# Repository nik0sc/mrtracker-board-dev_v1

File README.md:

# mrtracker-board (dev_v1)

## What is this?

This is the KiCAD schematic and board layout of MRTracker. BOM and centroid (pick and place) files are in the `assembly` directory.

MRTracker is a physical map of the MRT that tracks the location of trains in near real-time. It is a PCB with an array of LEDs on them and an ESP32 that gets the real-time location of trains. An LED will be lit for every train currently on the network. Currently the North-South and East-West lines are supported.

In the background, there is a web service that polls SMRT’s train API and transforms the arrival times of all lines at all stations into a map of individual trains on the network. (So, the accuracy of train locations is determined by the accuracy of these arrival timings.) The MRTracker board retrieves the map from this service periodically.

If you’ve seen traintrackr.io then this is something like that, but adapted for Singapore.

[Here is Geoff Marshall explaining traintrackr](https://www.youtube.com/watch?v=676xnII2OZg)

## Can I make it?

Sure, but firmware is not included. I made the board you see at the start of this README with [JLCPCB](https://jlcpcb.com/), they're pretty great.

**As-is**: No warranty express or implied of fitness for purpose. 

## Can I fork it, remix it, add the other lines, etc...?

Generally there is no copyright enforceable for hardware designs (weirdly there is an exemption for the highly secretive and competitive world of photolithography mask designs). So feel free.

## Known issues

- USB port GND pin is not connected (grounds through shield)

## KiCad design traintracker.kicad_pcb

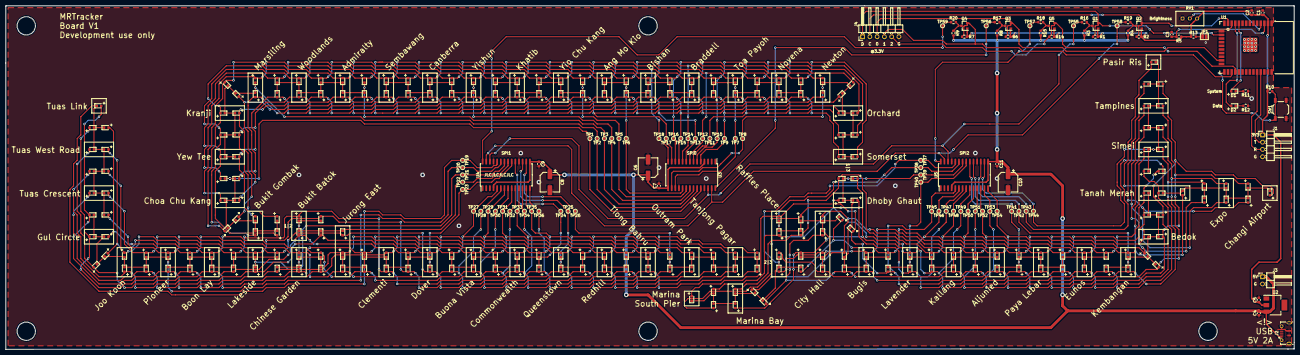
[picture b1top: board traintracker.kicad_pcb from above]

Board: 2 copper layers, 450.0 x 120.0 mm, 349 parts (0 on the bottom side), 82 nets.

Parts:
C1, C4, C5: 10uF; C_0603_1608Metric
C2, C7, C9, C11: 0.1uF; C_0603_1608Metric
C3: 1uF; C_0603_1608Metric
C6, C8, C10: 100uF; CP_Elec_6.3x5.3
D1, D3, D4, D5, D6, D7, D8, D9, D10, D11, D12, D13, D14, D15, D16, D17, D18, D19, D20, D21, D22, D23, D24, D25, D26, D27, D28, D29, D30, D31, D32, D33, D34, D35, D36, D37, D38, D39, D40, D41, D42, D43, D44, D45, D46, D47, D48, D49, D50, D51, D52, D53, D54, D55, D56, D57, D58, D59, D60, D61, D62, D63, D64, D65, D66, D67, D68, D69, D70, D71, D72, D73, D74, D75, D76, D77, D78, D79, D80, D81, D82, D118, D119, D120, D121, D122, D163, D164, D165, D166, D167, D168, D169, D173, D174, D175, D176, D178, D179, D182, D183, D184, D185, D186, D187: RED; LED_0603_1608Metric
D2, D83, D84, D85, D86, D87, D88, D89, D90, D91, D92, D93, D94, D95, D96, D97, D98, D99, D100, D101, D102, D103, D104, D105, D106, D107, D108, D109, D110, D111, D112, D113, D114, D115, D116, D117, D123, D124, D125, D126, D127, D128, D129, D130, D131, D132, D133, D134, D135, D136, D137, D138, D139, D140, D141, D142, D143, D144, D145, D146, D147, D148, D149, D150, D151, D152, D153, D154, D155, D156, D157, D158, D159, D160, D161, D162, D170, D171, D172, D177, D180, D181, D188, D189, D190, D191, D192, D193, D194, D195, D196, D197, D198, D199, D200, D201, D202, D203, D204, D205, D206, D207, D208, D209, D210, D211, D212, D213, D214, D215, D216, D217, D218, D219, D220, D221, D222, D223, D224, D225, D226, D227, D228, D229, D230, D231, D232, D233, D234, D235, D236, D237, D238, D239, D240, D241, D242: GREEN; LED_0603_1608Metric
J1: SERIAL; PinHeader_1x04_P2.54mm_Horizontal
J2: USB_B_Micro; USB_Micro-B_shouhan_microxnj
J3: 5V; PinHeader_1x02_P2.54mm_Horizontal
J4: LED_SPI_3.3; PinHeader_1x06_P2.54mm_Horizontal
JP1: MODE; SolderJumper-2_P1.3mm_Open_Pad1.0x1.5mm
Q1, Q2, Q3, Q4, Q5: Q_NMOS_GSD; SOT-23
R1, R2, R3, R4, R5, R6, R7, R8, R9, R10, R13, R14, R15: 10k; R_0603_1608Metric
R11, R12: 1k; R_0603_1608Metric
R16, R17, R18, R19, R20: 47; R_0603_1608Metric
RV1: 0-10k; Potentiometer_Bourns_3296W_Vertical
SW1: BOOT/RST; SW_SPST_TL3342
TP1, TP2, TP3, TP4, TP5, TP6, TP7, TP8, TP9, TP10, TP11, TP12, TP13, TP14, TP15, TP16, TP17, TP18, TP19, TP20, TP21, TP22, TP23, TP24, TP25, TP26, TP27, TP28, TP29, TP30, TP31, TP32, TP33, TP34, TP35, TP36, TP37, TP38, TP39, TP40, TP41, TP42, TP43, TP44, TP45, TP46, TP47, TP48, TP49, TP50, TP51, TP52, TP53, TP54: TestPoint; TestPoint_Pad_D1.0mm
TP55: MOSI_5V; TestPoint_Pad_D1.0mm
TP56: CS0_5V; TestPoint_Pad_D1.0mm
TP57: CS2_5V; TestPoint_Pad_D1.0mm
TP58: SCLK_5V; TestPoint_Pad_D1.0mm
TP59: CS1_5V; TestPoint_Pad_D1.0mm
U1: ESP32-WROOM-32
U2: LM1117-3.3; SOT-223
U3, U4, U5: TM1638; SOIC-28W_7.5x17.9mm_P1.27mm

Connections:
+3V3: C1.1, C2.1, C5.1, J1.1, Q1.1, Q2.1, Q3.1, Q4.1, Q5.1, R1.2, R2.2, R5.1, R6.2, R7.2, R10.1, R13.1, R14.2, RV1.1, U1.2, U2.2
+5V: C4.2, C6.1, C7.1, C8.1, C9.1, C10.1, C11.1, J2.1, J3.1, R3.2, R4.2, R8.2, R9.2, R15.2, U2.3, U3.4, U3.15, U4.4, U4.15, U5.4, U5.15
/RX: J1.3, U1.34
/TX: J1.2, U1.35
/grid1/GRID1: D3.1, D4.1, D5.1, D6.1, D7.1, D8.1, D9.1, D10.1, D11.1, D12.1, TP1.1, U3.24
/grid1/GRID2: D13.1, D14.1, D15.1, D16.1, D17.1, D18.1, D19.1, D20.1, D21.1, D22.1, TP2.1, U3.23
/grid1/GRID3: D23.1, D24.1, D25.1, D26.1, D27.1, D28.1, D29.1, D30.1, D31.1, D32.1, TP3.1, U3.22
/grid1/GRID4: D33.1, D34.1, D35.1, D36.1, D37.1, D38.1, D39.1, D40.1, D41.1, D42.1, TP4.1, U3.21
/grid1/GRID5: D43.1, D44.1, D45.1, D46.1, D47.1, D48.1, D49.1, D50.1, D51.1, D52.1, TP5.1, U3.20
/grid1/GRID6: D53.1, D54.1, D55.1, D56.1, D57.1, D58.1, D59.1, D60.1, D61.1, D62.1, TP6.1, U3.19
/grid1/GRID7: D63.1, D64.1, D65.1, D66.1, D67.1, D68.1, D69.1, D70.1, D71.1, D72.1, TP7.1, U3.17
/grid1/GRID8: D73.1, D74.1, D75.1, D76.1, D77.1, D78.1, D79.1, D80.1, D81.1, D82.1, TP8.1, U3.16
/grid1/SEG1: D3.2, D13.2, D23.2, D33.2, D43.2, D53.2, D63.2, D73.2, TP9.1, U3.5
/grid1/SEG2: D4.2, D14.2, D24.2, D34.2, D44.2, D54.2, D64.2, D74.2, TP10.1, U3.6
/grid1/SEG3: D5.2, D15.2, D25.2, D35.2, D45.2, D55.2, D65.2, D75.2, TP11.1, U3.7
/grid1/SEG4: D6.2, D16.2, D26.2, D36.2, D46.2, D56.2, D66.2, D76.2, TP12.1, U3.8
/grid1/SEG5: D7.2, D17.2, D27.2, D37.2, D47.2, D57.2, D67.2, D77.2, TP13.1, U3.9
/grid1/SEG6: D8.2, D18.2, D28.2, D38.2, D48.2, D58.2, D68.2, D78.2, TP14.1, U3.10
/grid1/SEG7: D9.2, D19.2, D29.2, D39.2, D49.2, D59.2, D69.2, D79.2, TP15.1, U3.11
/grid1/SEG8: D10.2, D20.2, D30.2, D40.2, D50.2, D60.2, D70.2, D80.2, TP16.1, U3.12
/grid1/SEG9: D11.2, D21.2, D31.2, D41.2, D51.2, D61.2, D71.2, D81.2, TP17.1, U3.13
/grid1/SEG10: D12.2, D22.2, D32.2, D42.2, D52.2, D62.2, D72.2, D82.2, TP18.1, U3.14
/grid2/GRID1: D83.1, D84.1, D85.1, D86.1, D87.1, D88.1, D89.1, D90.1, D91.1, D92.1, TP19.1, U4.24
/grid2/GRID2: D93.1, D94.1, D95.1, D96.1, D97.1, D98.1, D99.1, D100.1, D101.1, D102.1, TP20.1, U4.23
/grid2/GRID3: D103.1, D104.1, D105.1, D106.1, D107.1, D108.1, D109.1, D110.1, D111.1, D112.1, TP21.1, U4.22
/grid2/GRID4: D113.1, D114.1, D115.1, D116.1, D117.1, D118.1, D119.1, D120.1, D121.1, D122.1, TP22.1, U4.21
/grid2/GRID5: D123.1, D124.1, D125.1, D126.1, D127.1, D128.1, D129.1, D130.1, D131.1, D132.1, TP23.1, U4.20
/grid2/GRID6: D133.1, D134.1, D135.1, D136.1, D137.1, D138.1, D139.1, D140.1, D141.1, D142.1, TP24.1, U4.19
/grid2/GRID7: D143.1, D144.1, D145.1, D146.1, D147.1, D148.1, D149.1, D150.1, D151.1, D152.1, TP25.1, U4.17
/grid2/GRID8: D153.1, D154.1, D155.1, D156.1, D157.1, D158.1, D159.1, D160.1, D161.1, D162.1, TP26.1, U4.16
/grid2/SEG1: D83.2, D93.2, D103.2, D113.2, D123.2, D133.2, D143.2, D153.2, TP27.1, U4.5
/grid2/SEG2: D84.2, D94.2, D104.2, D114.2, D124.2, D134.2, D144.2, D154.2, TP28.1, U4.6
/grid2/SEG3: D85.2, D95.2, D105.2, D115.2, D125.2, D135.2, D145.2, D155.2, TP29.1, U4.7
/grid2/SEG4: D86.2, D96.2, D106.2, D116.2, D126.2, D136.2, D146.2, D156.2, TP30.1, U4.8
/grid2/SEG5: D87.2, D97.2, D107.2, D117.2, D127.2, D137.2, D147.2, D157.2, TP31.1, U4.9
/grid2/SEG6: D88.2, D98.2, D108.2, D118.2, D128.2, D138.2, D148.2, D158.2, TP32.1, U4.10
/grid2/SEG7: D89.2, D99.2, D109.2, D119.2, D129.2, D139.2, D149.2, D159.2, TP33.1, U4.11
/grid2/SEG8: D90.2, D100.2, D110.2, D120.2, D130.2, D140.2, D150.2, D160.2, TP34.1, U4.12
/grid2/SEG9: D91.2, D101.2, D111.2, D121.2, D131.2, D141.2, D151.2, D161.2, TP35.1, U4.13
/grid2/SEG10: D92.2, D102.2, D112.2, D122.2, D132.2, D142.2, D152.2, D162.2, TP36.1, U4.14
/grid3/GRID1: D163.1, D164.1, D165.1, D166.1, D167.1, D168.1, D169.1, D170.1, D171.1, D172.1, TP37.1, U5.24
/grid3/GRID2: D173.1, D174.1, D175.1, D176.1, D177.1, D178.1, D179.1, D180.1, D181.1, D182.1, TP38.1, U5.23
/grid3/GRID3: D183.1, D184.1, D185.1, D186.1, D187.1, D188.1, D189.1, D190.1, D191.1, D192.1, TP39.1, U5.22
/grid3/GRID4: D193.1, D194.1, D195.1, D196.1, D197.1, D198.1, D199.1, D200.1, D201.1, D202.1, TP40.1, U5.21
/grid3/GRID5: D203.1, D204.1, D205.1, D206.1, D207.1, D208.1, D209.1, D210.1, D211.1, D212.1, TP41.1, U5.20
/grid3/GRID6: D213.1, D214.1, D215.1, D216.1, D217.1, D218.1, D219.1, D220.1, D221.1, D222.1, TP42.1, U5.19
/grid3/GRID7: D223.1, D224.1, D225.1, D226.1, D227.1, D228.1, D229.1, D230.1, D231.1, D232.1, TP43.1, U5.17
/grid3/GRID8: D233.1, D234.1, D235.1, D236.1, D237.1, D238.1, D239.1, D240.1, D241.1, D242.1, TP44.1, U5.16
/grid3/SEG1: D163.2, D173.2, D183.2, D193.2, D203.2, D213.2, D223.2, D233.2, TP45.1, U5.5
/grid3/SEG2: D164.2, D174.2, D184.2, D194.2, D204.2, D214.2, D224.2, D234.2, TP46.1, U5.6
/grid3/SEG3: D165.2, D175.2, D185.2, D195.2, D205.2, D215.2, D225.2, D235.2, TP47.1, U5.7
/grid3/SEG4: D166.2, D176.2, D186.2, D196.2, D206.2, D216.2, D226.2, D236.2, TP48.1, U5.8
/grid3/SEG5: D167.2, D177.2, D187.2, D197.2, D207.2, D217.2, D227.2, D237.2, TP49.1, U5.9
/grid3/SEG6: D168.2, D178.2, D188.2, D198.2, D208.2, D218.2, D228.2, D238.2, TP50.1, U5.10
/grid3/SEG7: D169.2, D179.2, D189.2, D199.2, D209.2, D219.2, D229.2, D239.2, TP51.1, U5.11
/grid3/SEG8: D170.2, D180.2, D190.2, D200.2, D210.2, D220.2, D230.2, D240.2, TP52.1, U5.12
/grid3/SEG9: D171.2, D181.2, D191.2, D201.2, D211.2, D221.2, D231.2, D241.2, TP53.1, U5.13
/grid3/SEG10: D172.2, D182.2, D192.2, D202.2, D212.2, D222.2, D232.2, D242.2, TP54.1, U5.14
CS0_3.3V: J4.3, Q3.2, R6.1, U1.23
CS0_5V: R17.1, TP56.1, U3.28
CS1_3.3V: J4.4, Q4.2, R7.1, U1.27
CS1_5V: R20.1, TP59.1, U4.28
CS2_3.3V: J4.5, Q5.2, R14.1, U1.28
CS2_5V: R18.1, TP57.1, U5.28
GND: C1.2, C2.2, C3.2, C4.1, C5.2, C6.2, C7.2, C8.2, C9.2, C10.2, C11.2, J1.4, J2.5, J2.6, J3.2, J4.6, JP1.2, R11.1, R12.1, RV1.3, SW1.2, U1.1, U1.15, U1.38, U1.39, U2.1, U3.18, U3.25, U4.18, U4.25, U5.18, U5.25
MOSI_3.3V: J4.1, Q1.2, R1.1, U1.16
MOSI_5V: R16.1, TP55.1, U3.26, U4.26, U5.26
unnamed: C3.1, R5.2, U1.3
unnamed: D1.1, R11.2
unnamed: D1.2, U1.10
unnamed: D2.1, R12.2
unnamed: D2.2, U1.11
unnamed: JP1.1, R13.2, U1.12
unnamed: Q1.3, R3.1, R16.2
unnamed: Q2.3, R4.1, R19.2
unnamed: Q3.3, R8.1, R17.2
unnamed: Q4.3, R9.1, R20.2
unnamed: Q5.3, R15.1, R18.2
unnamed: R10.2, SW1.1, U1.25
unnamed: RV1.2, U1.4
SCLK_3.3V: J4.2, Q2.2, R2.1, U1.13
SCLK_5V: R19.1, TP58.1, U3.27, U4.27, U5.27

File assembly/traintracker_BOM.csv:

Comment,Designator,Footprint,LCSC
"10uF","C1,C4,C5","Capacitor_SMD:C_0603_1608Metric","C19702"
"0.1uF","C2,C7,C9,C11","Capacitor_SMD:C_0603_1608Metric","C14663"
"1uF","C3","Capacitor_SMD:C_0603_1608Metric","C15849"
"100uF","C6,C8,C10","Capacitor_SMD:CP_Elec_6.3x5.3","C134723"
"RED","D1,D3,D4,D5,D6,D7,D8,D9,D10,D11,D12,D13,D14,D15,D16,D17,D18,D19,D20,D21,D22,D23,D24,D25,D26,D27,D28,D29,D30,D31,D32,D33,D34,D35,D36,D37,D38,D39,D40,D41,D42,D43,D44,D45,D46,D47,D48,D49,D50,D51,D52,D53,D54,D55,D56,D57,D58,D59,D60,D61,D62,D63,D64,D65,D66,D67,D68,D69,D70,D71,D72,D73,D74,D75,D76,D77,D78,D79,D80,D81,D82,D118,D119,D120,D121,D122,D163,D164,D165,D166,D167,D168,D169,D173,D174,D175,D176,D178,D179,D182,D183,D184,D185,D186,D187","custom:LED_0603_1608Metric","C375444"
"GREEN","D2,D83,D84,D85,D86,D87,D88,D89,D90,D91,D92,D93,D94,D95,D96,D97,D98,D99,D100,D101,D102,D103,D104,D105,D106,D107,D108,D109,D110,D111,D112,D113,D114,D115,D116,D117,D123,D124,D125,D126,D127,D128,D129,D130,D131,D132,D133,D134,D135,D136,D137,D138,D139,D140,D141,D142,D143,D144,D145,D146,D147,D148,D149,D150,D151,D152,D153,D154,D155,D156,D157,D158,D159,D160,D161,D162,D170,D171,D172,D177,D180,D181,D188,D189,D190,D191,D192,D193,D194,D195,D196,D197,D198,D199,D200,D201,D202,D203,D204,D205,D206,D207,D208,D209,D210,D211,D212,D213,D214,D215,D216,D217,D218,D219,D220,D221,D222,D223,D224,D225,D226,D227,D228,D229,D230,D231,D232,D233,D234,D235,D236,D237,D238,D239,D240,D241,D242","custom:LED_0603_1608Metric","C72043"
"USB_B_Micro","J2","custom:USB_Micro-B_shouhan_microxnj","C404969"
"Q_NMOS_GSD","Q1,Q2,Q3,Q4,Q5","Package_TO_SOT_SMD:SOT-23","C8545"
"10k","R1,R2,R3,R4,R5,R6,R7,R8,R9,R10,R13,R14,R15","Resistor_SMD:R_0603_1608Metric","C25804"
"1k","R11,R12","Resistor_SMD:R_0603_1608Metric","C21190"
"47","R16,R17,R18,R19,R20","Resistor_SMD:R_0603_1608Metric","C23182"
"BOOT/RST","SW1","Button_Switch_SMD:SW_SPST_TL3342","C318884"
"ESP32-WROOM-32","U1","RF_Module:ESP32-WROOM-32","C701341"
"LM1117-3.3","U2","Package_TO_SOT_SMD:SOT-223","C6186"
"TM1638","U3,U4,U5","Package_SO:SOIC-28W_7.5x17.9mm_P1.27mm","C19187"
